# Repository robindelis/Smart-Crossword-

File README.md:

# Smart Crossword Board

A connected wooden crossword board: **older parents or grandparents play with physical wooden tiles on a board at home, while family members play their turns from an app on their phones.**

---

## What It Is

1. **Real Wooden Tiles**: 100 wooden letter tiles with hidden radio tags (NFC) inside.
2. **Simple for Older Players**: No phone needed at the board. A built-in screen and speaker announce opponent moves and show where to place tiles.
3. **Play from Anywhere**: Family members make moves and send short voice notes from their phones.
4. **Automatic Scoring**: The board checks the official dictionary and calculates double/triple scores automatically.

---

## System Overview

```
                                  [ Smart Crossword Board ]
                                             │
      ┌──────────────────────────────────────┼──────────────────────────────────────┐
      ▼                                      ▼                                      ▼
[ Tile Sensors ]                       [ Screen & Audio ]                     [ Power & Turntable ]
• 15x15 (225) antenna grid             • Dual-core microcontroller            • 3.7V 3000mAh battery
• 16-channel switch chips              • 4.3" high-contrast screen            • Magnetic power cable
• 13.56 MHz NFC reader                 • 3W speaker for voice audio           • 360° turntable ring
• 100 tagged wooden tiles              • Offline dictionary in memory         • Wooden enclosure
```

---

## Repository Folders

```
.
├── AGENTS.md               # Team rules and agent list
├── README.md               # This file
├── Project_Cockpit.canvas  # Visual board for Obsidian
├── docs/                   # Project documentation, specs, sourcing & state
│   ├── PROJECT_STATE.md    # Current phase, decisions, and roadmap
│   ├── Project_Tasks.md    # Task list (Kanban format)
│   └── ...                 # RFID specs, software architecture, candidate lists
├── .agents/
│   └── agents/             # Agent guidelines (hardware, code, sales, testing)
├── commercial/             # Market research, video script, ad templates
├── hardware/               # Circuit schematics and board layouts
├── firmware/               # Microcontroller code
├── software/               # Native Android companion app
└── tests/                  # Test scripts and benchmarks
```

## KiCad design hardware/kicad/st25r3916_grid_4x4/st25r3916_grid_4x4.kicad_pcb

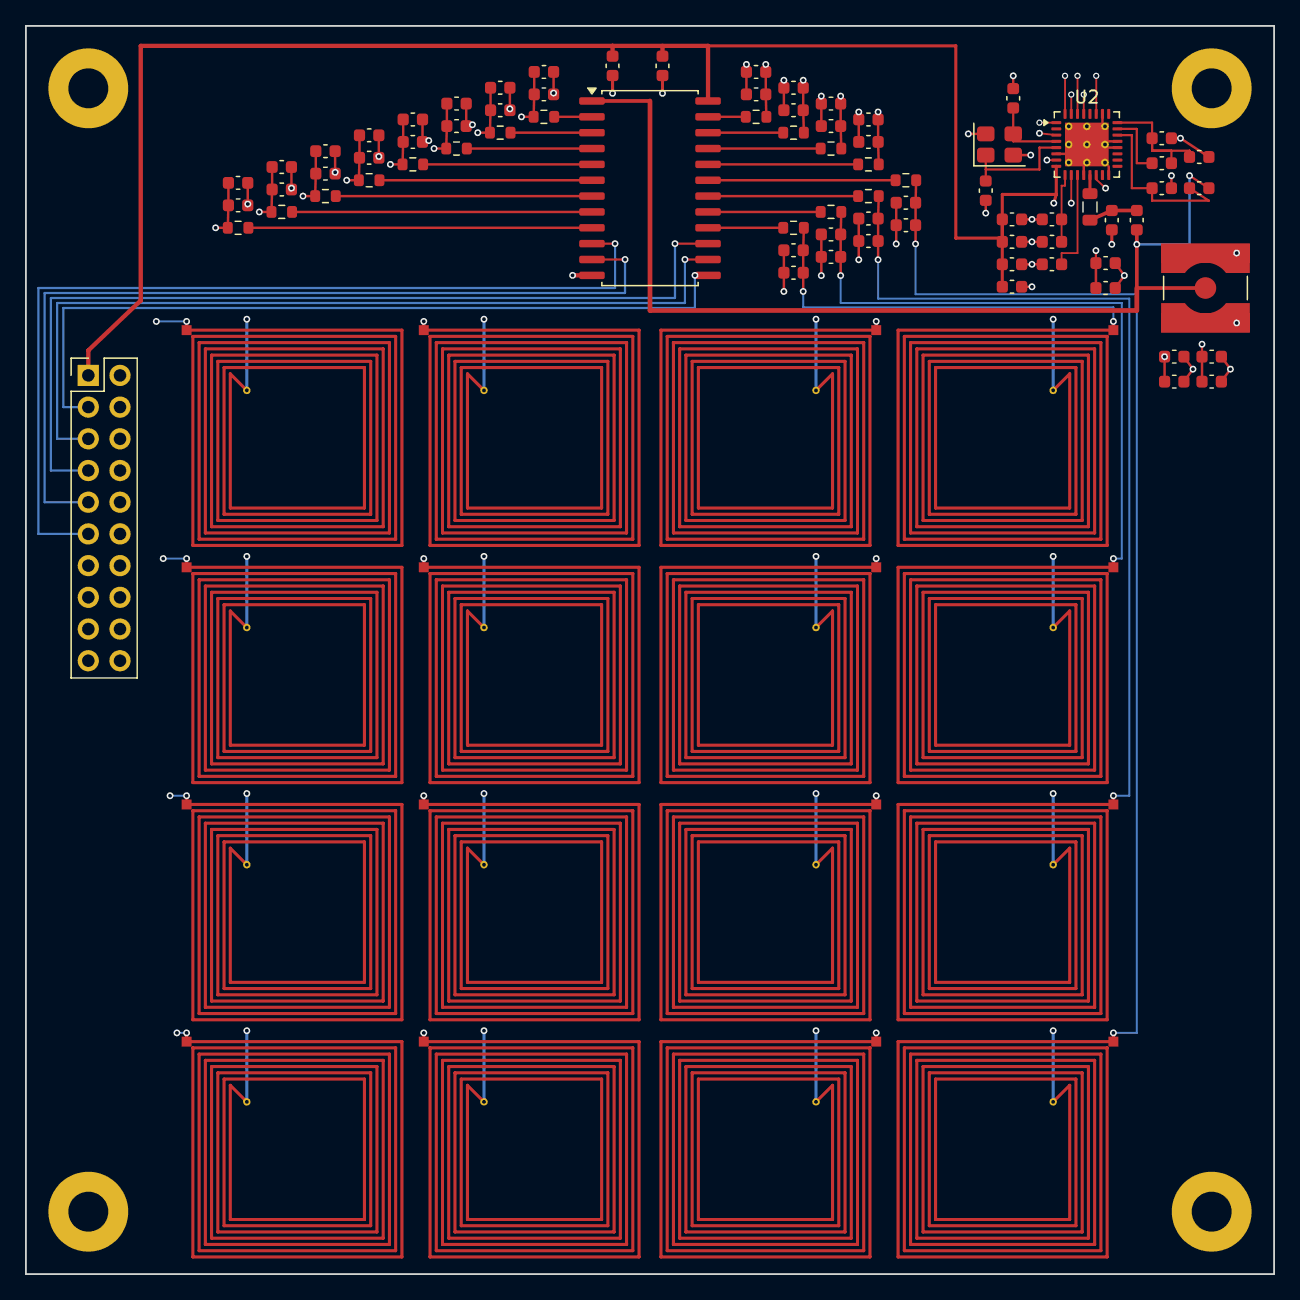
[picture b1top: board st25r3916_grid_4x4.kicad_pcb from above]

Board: 4 copper layers, 100.0 x 100.0 mm, 98 parts (0 on the bottom side), 58 nets.

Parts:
C17: 0.1uF; C_0603_1608Metric
C18, C26: 10uF; C_0603_1608Metric
C20, C24, C33, C35: 1uF; C_0603_1608Metric
C21, C25, C29, C31, C36: 10nF; C_0603_1608Metric
C22, C23: 12pF; C_0603_1608Metric
C27, C34: 100nF; C_0603_1608Metric
C28, C30, C32: 2.2uF; C_0603_1608Metric
C37: 180pF; C_0603_1608Metric
C38, C41: 150pF; C_0603_1608Metric
C39: 18pF; C_0603_1608Metric
C40: 10pF; C_0603_1608Metric
Ca1, Ca2, Ca3, Ca4, Ca5, Ca6, Ca7, Ca8, Ca9, Ca10, Ca11, Ca12, Ca13, Ca14, Ca15, Ca16: 100pF; C_0603_1608Metric
Cb1, Cb2, Cb3, Cb4, Cb5, Cb6, Cb7, Cb8, Cb9, Cb10, Cb11, Cb12, Cb13, Cb14, Cb15, Cb16: 22pF; C_0603_1608Metric
H1, H2, H3, H4: MountingHole_M3; MountingHole_3.2mm_M3_Pad
J1: Host_Header_2x10; PinHeader_2x10_P2.54mm_Vertical
J3: RF_TEST_SMA; SMA_Amphenol_132134-10_Vertical
L1, L2, L3, L4, L5, L6, L7, L8, L9, L10, L11, L12, L13, L14, L15, L16: 1.26uH
L17: 470nH; L_0805_2012Metric
R1, R2, R3, R4, R5, R6, R7, R8, R9, R10, R11, R12, R13, R14, R15, R16: 1.5R; R_0603_1608Metric
U1: CD74HC4067M; SOIC-24W_7.5x15.4mm_P1.27mm
U2: ST25R3916B-AQFT; VQFN-32-1EP_5x5mm_P0.5mm_EP3.5x3.5mm_ThermalVias
Y1: 27.12MHz; Crystal_SMD_3225-4Pin_3.2x2.5mm

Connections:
/+3.3V: J1.12, U2.1
/+5V: C17.1, C18.1, C26.1, C27.1, C30.1, C31.1, J1.1, U1.24, U2.8, U2.10
/AGDC: C35.1, C36.1, C38.2, U2.24
/GND: C17.2, C18.2, C20.2, C21.2, C22.2, C23.2, C24.2, C25.2, C26.2, C27.2, C28.2, C29.2, C30.2, C31.2, C32.2, C33.2, C34.2, C35.2, C36.2, C37.2, C41.2, Ca1.2, Ca2.2, Ca3.2, Ca4.2, Ca5.2, Ca6.2, Ca7.2, Ca8.2, Ca9.2, Ca10.2, Ca11.2, Ca12.2, Ca13.2, Ca14.2, Ca15.2, Ca16.2, Cb1.2, Cb2.2, Cb3.2, Cb4.2, Cb5.2, Cb6.2, Cb7.2, Cb8.2, Cb9.2, Cb10.2, Cb11.2, Cb12.2, Cb13.2, Cb14.2, Cb15.2, Cb16.2, H1.1, H2.1, H3.1, H4.1, J1.17, J1.18, J1.19, J1.20, J3.2, L1.2, L2.2, L3.2, L4.2, L5.2, L6.2, L7.2, L8.2, L9.2, L10.2, L11.2, L12.2, L13.2, L14.2, L15.2, L16.2, U1.12, U2.6, U2.12, U2.16, U2.20, U2.21, U2.26, U2.33, Y1.2, Y1.4
/MUX_EN: J1.7, U1.15
/MUX_S0: J1.11, U1.10
/MUX_S1: J1.9, U1.11
/MUX_S2: J1.5, U1.14
/MUX_S3: J1.3, U1.13
/OSC_IN: C23.1, U2.5, Y1.1
/OSC_OUT: C22.1, U2.4, Y1.3
/RFI1: C40.2, C41.1, U2.22
/RFI2: C38.1, U2.23
/RFO1: L17.1, U2.13
/RF_CH0: R13.2, U1.9
/RF_CH1: R9.2, U1.8
/RF_CH2: R5.2, U1.7
/RF_CH3: R1.2, U1.6
/RF_CH4: R14.2, U1.5
/RF_CH5: R10.2, U1.4
/RF_CH6: R6.2, U1.3
/RF_CH7: R2.2, U1.2
/RF_CH8: R15.2, U1.23
/RF_CH9: R11.2, U1.22
/RF_CH10: R7.2, U1.21
/RF_CH11: R3.2, U1.20
/RF_CH12: R16.2, U1.19
/RF_CH13: R12.2, U1.18
/RF_CH14: R8.2, U1.17
/RF_CH15: R4.2, U1.16
/RF_COIL_1: Ca1.1, Cb1.1, L1.1, R1.1
/RF_COIL_2: Ca2.1, Cb2.1, L2.1, R2.1
/RF_COIL_3: Ca3.1, Cb3.1, L3.1, R3.1
/RF_COIL_4: Ca4.1, Cb4.1, L4.1, R4.1
/RF_COIL_5: Ca5.1, Cb5.1, L5.1, R5.1
/RF_COIL_6: Ca6.1, Cb6.1, L6.1, R6.1
/RF_COIL_7: Ca7.1, Cb7.1, L7.1, R7.1
/RF_COIL_8: Ca8.1, Cb8.1, L8.1, R8.1
/RF_COIL_9: Ca9.1, Cb9.1, L9.1, R9.1
/RF_COIL_10: Ca10.1, Cb10.1, L10.1, R10.1
/RF_COIL_11: Ca11.1, Cb11.1, L11.1, R11.1
/RF_COIL_12: Ca12.1, Cb12.1, L12.1, R12.1
/RF_COIL_13: Ca13.1, Cb13.1, L13.1, R13.1
/RF_COIL_14: Ca14.1, Cb14.1, L14.1, R14.1
/RF_COIL_15: Ca15.1, Cb15.1, L15.1, R15.1
/RF_COIL_16: Ca16.1, Cb16.1, L16.1, R16.1
/RF_FLT: C37.1, C39.1, L17.2
/RF_SIG: C39.2, C40.1, J3.1, U1.1
/SPI_CS: J1.4, U2.29
/SPI_MISO: J1.10, U2.32
/SPI_MOSI: J1.8, U2.31
/SPI_SCK: J1.6, U2.30
/ST_IRQ: J1.2, U2.27
/VDD_A: C24.1, C25.1, U2.7
/VDD_AM: C32.1, U2.11
/VDD_D: C20.1, C21.1, U2.3
/VDD_DR: C33.1, C34.1, U2.14
/VDD_RF: C28.1, C29.1, U2.9

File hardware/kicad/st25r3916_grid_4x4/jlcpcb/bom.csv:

Comment,Designator,Footprint,LCSC Part #,Quantity
0.1uF,C17,C_0603_1608Metric,C14664,1
1.5R,"R1,R10,R11,R12,R13,R14,R15,R16,R2,R3,R4,R5,R6,R7,R8,R9",R_0603_1608Metric,C22790,16
100nF,"C27,C34",C_0603_1608Metric,C14664,2
100pF,"Ca1,Ca2,Ca3,Ca4,Ca5,Ca6,Ca7,Ca8,Ca9,Ca10,Ca11,Ca12,Ca13,Ca14,Ca15,Ca16",C_0603_1608Metric,C14663,16
10nF,"C21,C25,C29,C31,C36",C_0603_1608Metric,C57112,5
10pF,C40,C_0603_1608Metric,C1642,1
10uF,"C18,C26",C_0603_1608Metric,C19702,2
12pF,"C22,C23",C_0603_1608Metric,C1648,2
150pF,"C38,C41",C_0603_1608Metric,C1598,2
180pF,C37,C_0603_1608Metric,C1600,1
18pF,C39,C_0603_1608Metric,C1651,1
1uF,"C20,C24,C33,C35",C_0603_1608Metric,C15849,4
2.2uF,"C28,C30,C32",C_0603_1608Metric,C23630,3
22pF,"Cb1,Cb2,Cb3,Cb4,Cb5,Cb6,Cb7,Cb8,Cb9,Cb10,Cb11,Cb12,Cb13,Cb14,Cb15,Cb16",C_0603_1608Metric,C1653,16
27.12MHz,Y1,Crystal_SMD_3225-4Pin_3.2x2.5mm,C383929,1
470nH,L17,L_0805_2012Metric,C1045,1
CD74HC4067M,U1,SOIC-24W_7.5x15.4mm_P1.27mm,C109598,1
Host_Header_2x10,J1,PinHeader_2x10_P2.54mm_Vertical,,1
RF_TEST_SMA,J3,SMA_Amphenol_132134-10_Vertical,,1
ST25R3916B-AQFT,U2,VQFN-32-1EP_5x5mm_P0.5mm_EP3.5x3.5mm_ThermalVias,C2943312,1

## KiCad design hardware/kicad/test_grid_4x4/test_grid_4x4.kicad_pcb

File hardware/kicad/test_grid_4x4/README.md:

# Phase 1: 4x4 NFC Test Board

## 1. Purpose
This 4x4 circuit board is the Phase 1 test vehicle for the Smart Crossword Board project. It tests reading 16 RFID letter tiles through 2.0mm to 2.5mm hardwood before building the full 15x15 (225-cell) commercial board.

It verifies three physical requirements:
1. **Hardwood Penetration**: Reliable tag reads through 2.0mm–2.5mm oak or walnut veneer.
2. **Scan Speed**: Reading all 16 cells in under 40 milliseconds using an analog multiplexer.
3. **Cross-talk Isolation**: Zero false reads on neighboring empty cells when adjacent cells have tiles.

---

## 2. Key Specifications

| Parameter | Value | Notes |
| :--- | :--- | :--- |
| **Grid Dimensions** | 4 x 4 (16 cells) | Pitch: 19.0 mm (matches Scrabble tiles) |
| **Active Scan Area** | 76.0 mm x 76.0 mm | Centered on board |
| **PCB Dimensions** | 100.0 mm x 100.0 mm | Standard 10cm x 10cm low-cost pool |
| **Layers** | 4 layers | F.Cu (RF), In1.Cu (GND), In2.Cu (Pwr/Sig), B.Cu (Return/GND) |
| **Coil Outer Size** | 17.5 mm x 17.5 mm | Fits comfortably within 19mm square |
| **Coil Geometry** | 7 turns, 0.25mm trace, 0.25mm space | Planar square spiral on F.Cu |
| **Coil Inductance ($L$)** | **1.262 µH** | Wheeler model verified |
| **Tuning Capacitor ($C$)** | **100 pF** (50V C0G / NP0 0603) | Resonant frequency: 13.56 MHz |
| **Damping Resistor ($R$)** | **3.3 Ω** (1% 0603) | Target loaded Q-factor: 25 |
| **RF Multiplexer** | CD74HC4067SM96 (SOIC-24) | 16-channel analog switch (LCSC C7406) |
| **Mounting** | 4x M3 screw holes (3.2mm drill) | 5.0mm inset from corners |

---

## 3. Connector Pinouts

### J1: Host Controller Header (2x10, 2.54mm Pitch)
Connects directly to an ESP32-S3 DevKit or breadboard:

| Pin | Net | Function | Pin | Net | Function |
| :--- | :--- | :--- | :--- | :--- | :--- |
| **1** | +3.3V | Power In | **2** | +3.3V | Power In |
| **3** | MUX_S3 | Address bit 3 | **4** | GPIO_AUX | Spare tactile button / LED |
| **5** | MUX_S2 | Address bit 2 | **6** | I2C_SDA | Spare I2C data |
| **7** | MUX_EN | MUX active-low enable | **8** | I2C_SCL | Spare I2C clock |
| **9** | MUX_S1 | Address bit 1 | **10** | NFC_IRQ | NFC interrupt |
| **11** | MUX_S0 | Address bit 0 | **12** | NFC_RST | NFC reset |
| **13** | GND | Ground | **14** | SPI_MOSI | NFC SPI data out |
| **15** | GND | Ground | **16** | SPI_CS | NFC SPI chip select |
| **17** | GND | Ground | **18** | SPI_SCK | NFC SPI clock |
| **19** | GND | Ground | **20** | SPI_MISO | NFC SPI data in |

### J2: NFC Transceiver Header (1x10, 2.54mm Pitch)
Connects to an ST25R3916 or PN532 transceiver breakout:
1. `RF_SIG` (Multiplexer common RF output/input)
2. `GND`
3. `+3.3V`
4. `GND`
5. `SPI_SCK`
6. `SPI_MISO`
7. `SPI_MOSI`
8. `SPI_CS`
9. `NFC_IRQ`
10. `NFC_RST`

### J3: SMA RF Test Port
Standard 50Ω SMA coaxial connector wired to `RF_SIG` for connecting an oscilloscope or Vector Network Analyzer (VNA) during bench characterization.

---

## 4. Verification & DRC Status (KiCad 10.0.6)

* **Design Rule Check (DRC)**: **0 errors, 0 warnings, 0 violations**.
* **Unconnected Items**: **0 unconnected nets** (all 49 nets fully routed).
* **Layer Stackup**:
  * **F.Cu**: 16 planar spiral coils (1.26 µH, 7 turns), RF_SIG 50Ω trace, 0603 matching network components.
  * **In1.Cu**: Continuous solid GND plane with 16 dedicated keepout apertures ($18.5\text{mm} \times 18.5\text{mm}$) preventing RF eddy current damping.
  * **In2.Cu**: 100% planar coil feed routing for Columns A, B, C, and D, plus SPI bus lines.
  * **B.Cu**: Bottom GND plane with thermal relief spokes to coil centers, concentric MUX control lines, and +3.3V power bus.

---

## 5. Bill of Materials (BOM)

| Designator | Description | Footprint | LCSC Part # | Unit Price (100 qty) |
| :--- | :--- | :--- | :--- | :--- |
| **U1** | CD74HC4067SM96 16-Ch MUX | SOIC-24 | C496123 | $0.28 |
| **C1–C16** | 100pF 50V C0G 5% | 0603 | C14665 | $0.005 |
| **R1–R16** | 3.3Ω 1% 1/10W | 0603 | C22979 | $0.003 |
| **C17** | 0.1µF 50V X7R 10% (Decoupling) | 0603 | C14663 | $0.003 |
| **C18** | 10µF 10V X5R 10% (Decoupling) | 0805 | C15850 | $0.015 |
| **J1** | 2x10 2.54mm Male Pin Header | THT 2x10 | C22588 | $0.15 |
| **J2** | 1x10 2.54mm Male Pin Header | THT 1x10 | C22585 | $0.08 |
| **J3** | SMA End Launch / Edge Female | SMA-TH | C2837267 | $0.65 |
| **H1–H4** | M3 Mounting Holes | 3.2mm PTH | N/A | $0.00 |

**Total BOM cost for 4x4 test board**: ~$1.45 (excluding PCB fab).

---

## 6. How to Open and Review in KiCad

1. Open your Linux application launcher.
2. Select **KiCad (EDA Suite)** (the top entry with the blue icon).
3. In KiCad, go to **File -> Open Project...**.
4. Browse to `hardware/kicad/test_grid_4x4/test_grid_4x4.kicad_pro`.
5. Double-click `test_grid_4x4.kicad_sch` to view the schematic, or `test_grid_4x4.kicad_pcb` to view the board layout.
6. In the PCB editor, press **Alt + 3** (or menu **View -> 3D Viewer**) to interact with the 3D model.

---

## 7. Prototype (4x4) Shopping List Compatibility & Wiring Guide

This section verifies compatibility with the components procured in [[Prototype_4x4_Shopping_List|Prototype 4x4 Shopping List]]:

### Component Compatibility Matrix

| Shopping List Item | Selected Model | PCB Compatibility | Connection / Assembly Notes |
| :--- | :--- | :--- | :--- |
| **Letter Tiles (16 needed)** | 200 Pcs Wooden Scrabble Tiles (`B0GH7LXL2K`) | ✅ **100% Compatible** | 19.0 x 19.0 x 4.8 mm wood tiles align 1:1 with the 19.0mm PCB coil pitch. |
| **13.56 MHz NFC Tags** | 60 Pcs NTAG213 Stickers 25mm (`B0HC2ZKQLQ`) | ✅ **100% Compatible (RF)** | 13.56 MHz ISO 14443A matches resonant LC tank. For bench testing, 25mm stickers can be affixed centered on tiles or test veneer. |
| **Host Microcontroller** | ESP32-S3 DevKitC-1 N16R8 (`B0GXF14RRM`) | ✅ **100% Compatible** | 3.3V logic matches +3.3V rail. Connects to J1 via 20-pin IDC ribbon or Dupont jumper wires. |
| **16-Ch Multiplexer** | DollaTek CD74HC4067 Breakout (`B07PPKRVGW`) | ⚠️ **Footprint Variant Note** | PCB footprint U1 is **SOIC-24 SMD** (`CD74HC4067SM96`, LCSC C7406) for JLCPCB PCBA. The Amazon DollaTek breakout module (24-pin DIP) is for breadboard testing. Order JLCPCB PCBA or bare SOIC-24 IC for this PCB. |
| **NFC Reader Module** | PN532 V3 RFID/NFC Breakout Kit (`B0C9DTJMLQ`) | ⚠️ **RF Tap Required** | Connect SPI signals (SCK, MISO, MOSI, SS/CS, IRQ, RST, 3.3V, GND) to J2 via Dupont leads. To drive PCB coils, link the PN532 RF stage to J3 (SMA) or J2 Pin 1 (`RF_SIG`) via a 50Ω coaxial pigtail. |
| **Rotating Turntable** | QWORK Square Bearing 71x71mm (`B0B3X7R961`) | ✅ **100% Compatible** | Mounts centered underneath the 3D-printed base enclosure tray; zero interference with PCB. |
| **Color Display Screen** | 3.5" TFT SPI 480x320 (`B0BZXX1QFM`) | ✅ **100% Compatible** | Off-board peripheral wired directly to ESP32-S3 host GPIOs. |
| **Audio DAC Amp & Speaker** | MAX98357A I2S Amp (`B0F21T7Q3P`) + 40mm 4Ω Speaker | ✅ **100% Compatible** | Off-board I2S peripheral wired directly to ESP32-S3 host GPIOs. |
| **Hardware Fasteners** | 440 Pcs M3 Button Head Screws & Nuts (`B0B3MGZ7T2`) | ✅ **100% Compatible** | M3x8 / M3x10 screws seat perfectly in the 4x 3.2mm corner mounting holes (H1–H4). |
| **Anti-Skid Bumper Feet** | Silicone Bumper Feet 10mm (`B08GKP4311`) | ✅ **100% Compatible** | Fits bottom locating recesses in 3D-printed base enclosure. |

### J1 (ESP32-S3 Host) Wiring Map

| Header J1 Pin | Net | ESP32-S3 DevKit Pin | Function |
| :--- | :--- | :--- | :--- |
| **Pin 1, 2** | `+3.3V` | `3V3` | Power Supply |
| **Pin 3** | `MUX_S3` | `GPIO 4` | Multiplexer Address Bit 3 |
| **Pin 5** | `MUX_S2` | `GPIO 5` | Multiplexer Address Bit 2 |
| **Pin 7** | `MUX_EN` | `GPIO 6` | Multiplexer Enable (Active Low) |
| **Pin 9** | `MUX_S1` | `GPIO 7` | Multiplexer Address Bit 1 |
| **Pin 11** | `MUX_S0` | `GPIO 15` | Multiplexer Address Bit 0 |
| **Pin 13, 15, 17, 19** | `GND` | `GND` | Ground Reference |
| **Pin 4** | `GPIO_AUX` | `GPIO 16` | Spare / Tactile Button / LED |
| **Pin 6** | `I2C_SDA` | `GPIO 8` | Spare I2C Data |
| **Pin 8** | `I2C_SCL` | `GPIO 9` | Spare I2C Clock |
| **Pin 10** | `NFC_IRQ` | `GPIO 10` | NFC Reader Interrupt |
| **Pin 12** | `NFC_RST` | `GPIO 11` | NFC Reader Reset |
| **Pin 14** | `SPI_MOSI`| `GPIO 13` | SPI Data Host -> NFC |
| **Pin 16** | `SPI_CS` | `GPIO 14` | SPI Chip Select |
| **Pin 18** | `SPI_SCK` | `GPIO 12` | SPI Clock |
| **Pin 20** | `SPI_MISO`| `GPIO 21` | SPI Data NFC -> Host |

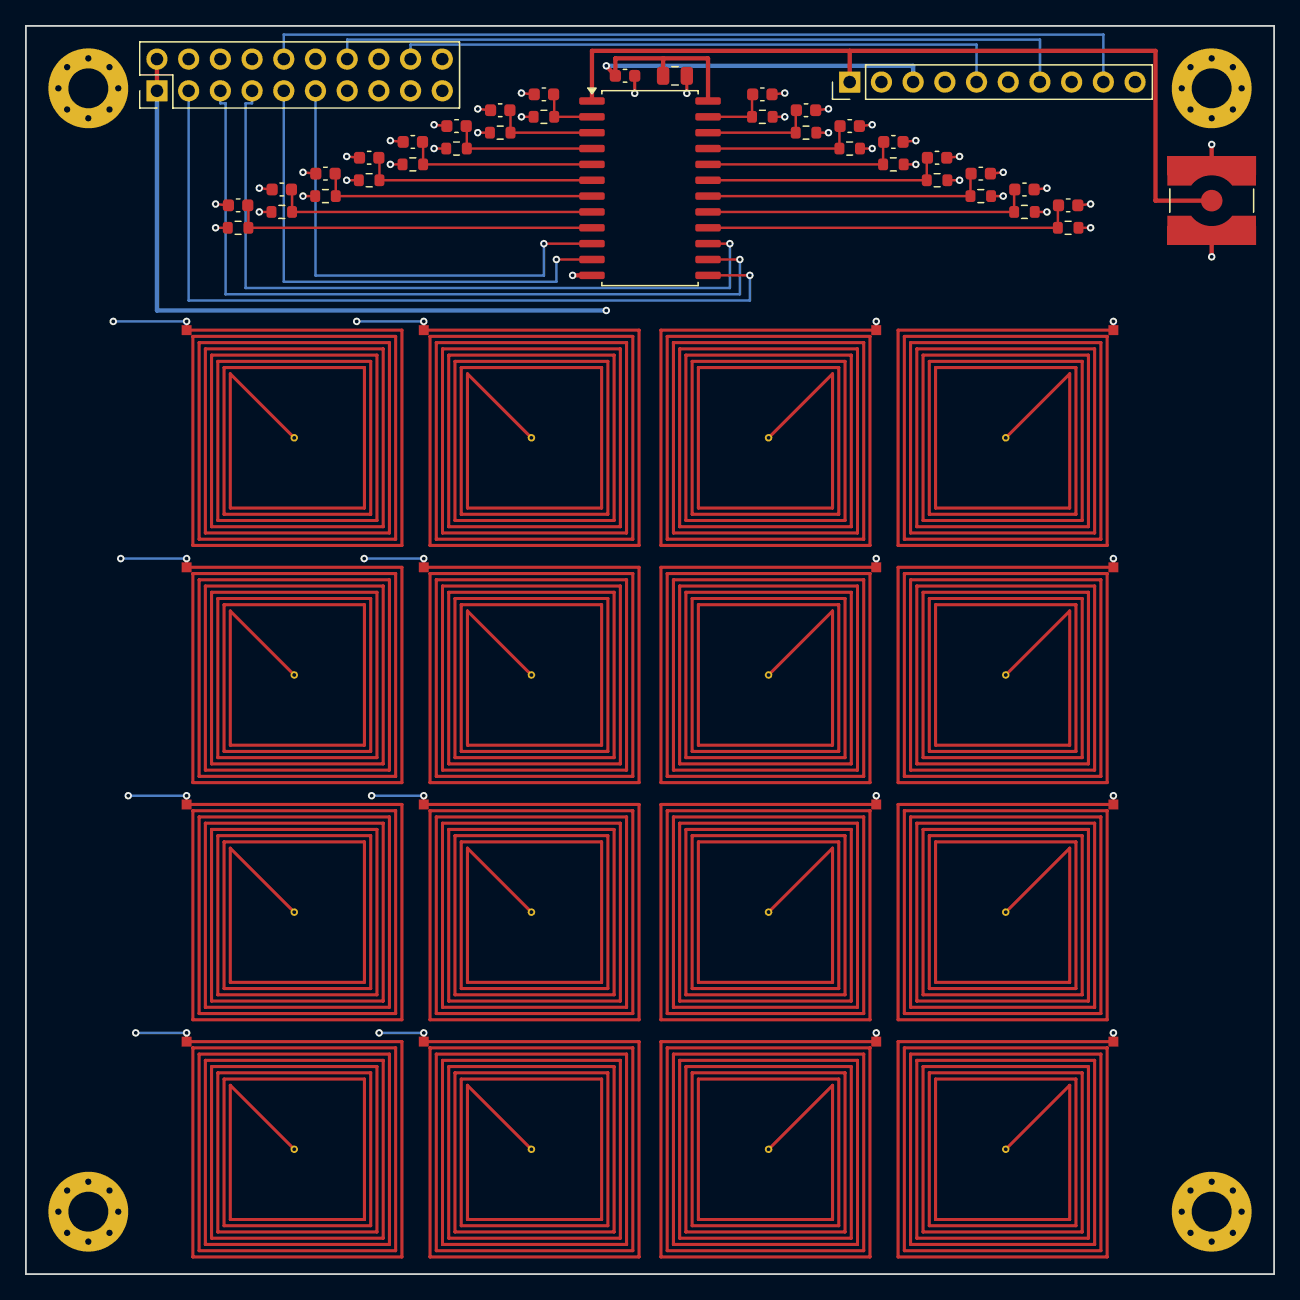
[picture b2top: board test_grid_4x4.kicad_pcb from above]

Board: 4 copper layers, 100.0 x 100.0 mm, 58 parts (0 on the bottom side), 46 nets.

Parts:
C1, C2, C3, C4, C5, C6, C7, C8, C9, C10, C11, C12, C13, C14, C15, C16: 100pF; C_0603_1608Metric
C17: 0.1uF; C_0603_1608Metric
C18: 10uF; C_0805_2012Metric
H1, H2, H3, H4: MountingHole_M3; MountingHole_3.2mm_M3_Pad_Via
J1: HOST_BUS; PinHeader_2x10_P2.54mm_Vertical
J2: NFC_MODULE; PinHeader_1x10_P2.54mm_Vertical
J3: RF_TEST; SMA_Amphenol_132134-10_Vertical
L1, L2, L3, L4, L5, L6, L7, L8, L9, L10, L11, L12, L13, L14, L15, L16: 1.26uH
R1, R2, R3, R4, R5, R6, R7, R8, R9, R10, R11, R12, R13, R14, R15, R16: 3.3; R_0603_1608Metric
U1: CD74HC4067M; SOIC-24W_7.5x15.4mm_P1.27mm

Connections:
+3.3V: C17.1, C18.1, J1.1, J1.2, J2.3, U1.24
GND: C1.2, C2.2, C3.2, C4.2, C5.2, C6.2, C7.2, C8.2, C9.2, C10.2, C11.2, C12.2, C13.2, C14.2, C15.2, C16.2, C17.2, C18.2, H1.1, H2.1, H3.1, H4.1, J1.13, J1.15, J1.17, J1.19, J2.2, J2.4, J3.2, L1.2, L2.2, L3.2, L4.2, L5.2, L6.2, L7.2, L8.2, L9.2, L10.2, L11.2, L12.2, L13.2, L14.2, L15.2, L16.2, U1.12
MUX_EN: J1.7, U1.15
MUX_S0: J1.11, U1.10
MUX_S1: J1.9, U1.11
MUX_S2: J1.5, U1.14
MUX_S3: J1.3, U1.13
NFC_IRQ: J1.10, J2.9
NFC_RST: J1.12, J2.10
RF_CH0: C13.1, R13.1, U1.9
RF_CH1: C9.1, R9.1, U1.8
RF_CH2: C5.1, R5.1, U1.7
RF_CH3: C1.1, R1.1, U1.6
RF_CH4: C14.1, R14.1, U1.5
RF_CH5: C10.1, R10.1, U1.4
RF_CH6: C6.1, R6.1, U1.3
RF_CH7: C2.1, R2.1, U1.2
RF_CH8: C15.1, R15.1, U1.23
RF_CH9: C11.1, R11.1, U1.22
RF_CH10: C7.1, R7.1, U1.21
RF_CH11: C3.1, R3.1, U1.20
RF_CH12: C16.1, R16.1, U1.19
RF_CH13: C12.1, R12.1, U1.18
RF_CH14: C8.1, R8.1, U1.17
RF_CH15: C4.1, R4.1, U1.16
RF_COIL_1: L1.1, R1.2
RF_COIL_2: L2.1, R2.2
RF_COIL_3: L3.1, R3.2
RF_COIL_4: L4.1, R4.2
RF_COIL_5: L5.1, R5.2
RF_COIL_6: L6.1, R6.2
RF_COIL_7: L7.1, R7.2
RF_COIL_8: L8.1, R8.2
RF_COIL_9: L9.1, R9.2
RF_COIL_10: L10.1, R10.2
RF_COIL_11: L11.1, R11.2
RF_COIL_12: L12.1, R12.2
RF_COIL_13: L13.1, R13.2
RF_COIL_14: L14.1, R14.2
RF_COIL_15: L15.1, R15.2
RF_COIL_16: L16.1, R16.2
RF_SIG: J2.1, J3.1, U1.1
SPI_CS: J1.16, J2.8
SPI_MISO: J1.20, J2.6
SPI_MOSI: J1.14, J2.7
SPI_SCK: J1.18, J2.5

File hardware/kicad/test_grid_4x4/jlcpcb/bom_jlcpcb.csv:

Comment,Designator,Footprint,LCSC Part #
100pF 50V C0G 5%,"C1, C2, C3, C4, C5, C6, C7, C8, C9, C10, C11, C12, C13, C14, C15, C16",C_0603_1608Metric,C14405
3.3Ω 1% 1/10W,"R1, R2, R3, R4, R5, R6, R7, R8, R9, R10, R11, R12, R13, R14, R15, R16",R_0603_1608Metric,C22971
0.1uF 50V X7R 10%,C17,C_0603_1608Metric,C14663
10uF 10V X5R 10%,C18,C_0805_2012Metric,C15850
CD74HC4067SM96 16-Ch MUX,U1,SOIC-24W_7.5x15.4mm_P1.27mm,C7406

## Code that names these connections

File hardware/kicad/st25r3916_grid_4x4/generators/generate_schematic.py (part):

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\t\t\t(pin power_in line (at -20.32 -12.70 0) (length 2.54) (name "VDD_TX" (effects (font (size 1.27 1.27)))) (number "10" (effects (font (size 1.27 1.27)))))
\t\t\t(pin power_out line (at 20.32 7.62 180) (length 2.54) (name "VDD_AM" (effects (font (size 1.27 1.27)))) (number "11" (effects (font (size 1.27 1.27)))))
\t\t\t(pin power_in line (at -5.08 25.4 270) (length 2.54) (name "GND_DR1" (effects (font (size 1.27 1.27)))) (number "12" (effects (font (size 1.27 1.27)))))
\t\t\t(pin output line (at 20.32 -17.78 180) (length 2.54) (name "RFO1" (effects (font (size 1.27 1.27)))) (number "13" (effects (font (size 1.27 1.27)))))
\t\t\t(pin power_out line (at 20.32 2.54 180) (length 2.54) (name "VDD_DR" (effects (font (size 1.27 1.27)))) (number "14" (effects (font (size 1.27 1.27)))))
\t\t\t(pin output line (at 20.32 -15.24 180) (length 2.54) (name "RFO2" (effects (font (size 1.27 1.27)))) (number "15" (effects (font (size 1.27 1.27)))))
\t\t\t(pin power_in line (at 0.00 25.4 270) (length 2.54) (name "GND_DR2" (effects (font (size 1.27 1.27)))) (number "16" (effects (font (size 1.27 1.27)))))
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\t\t\t(pin passive line (at -2.54 -25.4 90) (length 2.54) (name "AAT_B" (effects (font (size 1.27 1.27)))) (number "19" (effects (font (size 1.27 1.27)))))
\t\t\t(pin input line (at -20.32 12.70 0) (length 2.54) (name "I2C_EN" (effects (font (size 1.27 1.27)))) (number "20" (effects (font (size 1.27 1.27)))))
\t\t\t(pin power_in line (at 5.08 25.4 270) (length 2.54) (name "VSS" (effects (font (size 1.27 1.27)))) (number "21" (effects (font (size 1.27 1.27)))))
\t\t\t(pin input line (at 20.32 -10.16 180) (length 2.54) (name "RFI1" (effects (font (size 1.27 1.27)))) (number "22" (effects (font (size 1.27 1.27)))))
\t\t\t(pin input line (at 20.32 -7.62 180) (length 2.54) (name "RFI2" (effects (font (size 1.27 1.27)))) (number "23" (effects (font (size 1.27 1.27)))))
\t\t\t(pin power_out line (at 20.32 -2.54 180) (length 2.54) (name "AGDC" (effects (font (size 1.27 1.27)))) (number "24" (effects (font (size 1.27 1.27)))))
\t\t\t(pin passive line (at 2.54 -25.4 90) (length 2.54) (name "TAD1" (effects (font (size 1.27 1.27)))) (number "25" (effects (font (size 1.27 1.27)))))
\t\t\t(pin power_in line (at 10.16 25.4 270) (length 2.54) (name "GND_A" (effects (font (size 1.27 1.27)))) (number "26" (effects (font (size 1.27 1.27)))))
\t\t\t(pin output line (at -20.32 7.62 0) (length 2.54) (name "IRQ" (effects (font (size 1.27 1.27)))) (number "27" (effects (font (size 1.27 1.27)))))
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    connect_pin(u2_x, u2_y, pins_st25, 1, "+3.3V", -5.08, 0, 180)
    connect_pin(u2_x, u2_y, pins_st25, 8, "+5V", -5.08, 0, 180)
    connect_pin(u2_x, u2_y, pins_st25, 10, "+5V", -5.08, 0, 180)
    connect_pin(u2_x, u2_y, pins_st25, 29, "SPI_CS", -5.08, 0, 180)
    connect_pin(u2_x, u2_y, pins_st25, 30, "SPI_SCK", -5.08, 0, 180)
    connect_pin(u2_x, u2_y, pins_st25, 31, "SPI_MOSI", -5.08, 0, 180)
    connect_pin(u2_x, u2_y, pins_st25, 32, "SPI_MISO", -5.08, 0, 180)
    connect_pin(u2_x, u2_y, pins_st25, 27, "ST_IRQ", -5.08, 0, 180)
    connect_pin(u2_x, u2_y, pins_st25, 20, "GND", -5.08, 0, 180) # I2C_EN = GND for SPI mode

    nc_pin(u2_x, u2_y, pins_st25, 2)  # TAD2
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    nc_pin(u2_x, u2_y, pins_st25, 25) # TAD1

    # RF and Decoupling outputs
    connect_pin(u2_x, u2_y, pins_st25, 13, "RFO1", 5.08, 0, 0)
    connect_pin(u2_x, u2_y, pins_st25, 22, "RFI1", 5.08, 0, 0)
    connect_pin(u2_x, u2_y, pins_st25, 23, "RFI2", 5.08, 0, 0)
    connect_pin(u2_x, u2_y, pins_st25, 24, "AGDC", 5.08, 0, 0)
    connect_pin(u2_x, u2_y, pins_st25, 14, "VDD_DR", 5.08, 0, 0)
    connect_pin(u2_x, u2_y, pins_st25, 9, "VDD_RF", 5.08, 0, 0)
    connect_pin(u2_x, u2_y, pins_st25, 11, "VDD_AM", 5.08, 0, 0)
    connect_pin(u2_x, u2_y, pins_st25, 3, "VDD_D", 5.08, 0, 0)
    connect_pin(u2_x, u2_y, pins_st25, 7, "VDD_A", 5.08, 0, 0)
    connect_pin(u2_x, u2_y, pins_st25, 4, "OSC_OUT", 5.08, 0, 0)
    connect_pin(u2_x, u2_y, pins_st25, 5, "OSC_IN", 5.08, 0, 0)

    # Grounds
    connect_pin(u2_x, u2_y, pins_st25, 6, "GND", 0, 5.08, 270)
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\t\t(pin "4" (uuid "{gen_uuid()}"))
\t\t(instances (project "" (path "/{root_uuid}" (reference "Y1") (unit 1))))
\t)''')
    connect_pin(y1_x, y1_y, pins_xtal, 1, "OSC_OUT", 0, -2.54, 90)
    connect_pin(y1_x, y1_y, pins_xtal, 2, "GND", 2.54, 0, 0)
    connect_pin(y1_x, y1_y, pins_xtal, 3, "OSC_IN", 0, 2.54, 270)
    connect_pin(y1_x, y1_y, pins_xtal, 4, "GND", -2.54, 0, 180)

    # C22 (12pF), C23 (12pF)
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\t)''')
    # Note: L symbol rotated 90 deg -> pin 1 is at (-3.81, 0), pin 2 is at (3.81, 0)
    add_wire(l17_x - 3.81, l17_y, l17_x - 7.62, l17_y)
    add_label("RFO1", l17_x - 7.62, l17_y, 180)
    add_wire(l17_x + 3.81, l17_y, l17_x + 7.62, l17_y)
    add_label("RF_FLT", l17_x + 7.62, l17_y, 0)

    # C37: 180pF EMC filter capacitor to GND
    c37_x, c37_y = 76.2, 147.32
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\t\t(pin "2" (uuid "{gen_uuid()}"))
\t\t(instances (project "" (path "/{root_uuid}" (reference "C37") (unit 1))))
\t)''')
    connect_pin(c37_x, c37_y, pins_c, 1, "RF_FLT", 0, -2.54, 90)
    connect_pin(c37_x, c37_y, pins_c, 2, "GND", 0, 2.54, 270)

    # C39: 18pF Series Matching Capacitor (between RF_FLT and RF_SIG)
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\t\t(instances (project "" (path "/{root_uuid}" (reference "C39") (unit 1))))
\t)''')
    add_wire(c39_x - 3.81, c39_y, c39_x - 7.62, c39_y)
    add_label("RF_FLT", c39_x - 7.62, c39_y, 180)
    add_wire(c39_x + 3.81, c39_y, c39_x + 7.62, c39_y)
    add_label("RF_SIG", c39_x + 7.62, c39_y, 0)

    # Receiver Capacitive Divider: C40 (10pF), C41 (150pF), C38 (150pF)
    # C40 between RF_SIG and RFI1
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\t\t(instances (project "" (path "/{root_uuid}" (reference "C40") (unit 1))))
\t)''')
    add_wire(c40_x - 3.81, c40_y, c40_x - 7.62, c40_y)
    add_label("RF_SIG", c40_x - 7.62, c40_y, 180)
    add_wire(c40_x + 3.81, c40_y, c40_x + 7.62, c40_y)
    add_label("RFI1", c40_x + 7.62, c40_y, 0)

    # C41 (150pF between RFI1 and GND)
    c41_x, c41_y = 76.2, 177.8
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\t\t(pin "2" (uuid "{gen_uuid()}"))
\t\t(instances (project "" (path "/{root_uuid}" (reference "C41") (unit 1))))
\t)''')
    connect_pin(c41_x, c41_y, pins_c, 1, "RFI1", 0, -2.54, 90)
    connect_pin(c41_x, c41_y, pins_c, 2, "GND", 0, 2.54, 270)

    # C38 (150pF between RFI2 and AGDC)
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\t\t(pin "2" (uuid "{gen_uuid()}"))
\t\t(instances (project "" (path "/{root_uuid}" (reference "C38") (unit 1))))
\t)''')
    connect_pin(c38_x, c38_y, pins_c, 1, "RFI2", 0, -2.54, 90)
    connect_pin(c38_x, c38_y, pins_c, 2, "AGDC", 0, 2.54, 270)

    # 6. Multiplexer U1 (CD74HC4067M) at (177.8, 147.32)
    u1_x, u1_y = 177.8, 147.32
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\t\t(instances (project "" (path "/{root_uuid}" (reference "U1") (unit 1))))
\t)''')

    connect_pin(u1_x, u1_y, pins_mux, 1, "RF_SIG", -5.08, 0, 180)
    connect_pin(u1_x, u1_y, pins_mux, 24, "+5V", 0, -5.08, 90)
    connect_pin(u1_x, u1_y, pins_mux, 12, "GND", 0, 5.08, 270)
    connect_pin(u1_x, u1_y, pins_mux, 10, "MUX_S0", -5.08, 0, 180)
    connect_pin(u1_x, u1_y, pins_mux, 11, "MUX_S1", -5.08, 0, 180)
    connect_pin(u1_x, u1_y, pins_mux, 14, "MUX_S2", -5.08, 0, 180)
    connect_pin(u1_x, u1_y, pins_mux, 13, "MUX_S3", -5.08, 0, 180)
    connect_pin(u1_x, u1_y, pins_mux, 15, "MUX_EN", -5.08, 0, 180)

    # Decoupling caps for U1: C17 (0.1uF), C18 (10uF)
    for c_ref, c_val, cx, lcsc in [("C17", "0.1uF", 160.02, "C14663"), ("C18", "10uF", 147.32, "C15850")]:
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\t\t(pin "2" (uuid "{gen_uuid()}"))
\t\t(instances (project "" (path "/{root_uuid}" (reference "J3") (unit 1))))
\t)''')
    connect_pin(sma_x, sma_y, pins_sma, 1, "RF_SIG", -5.08, 0, 180)
    connect_pin(sma_x, sma_y, pins_sma, 2, "GND", 5.08, 0, 0)

    # 9. 4x Mounting Holes H1..H4
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
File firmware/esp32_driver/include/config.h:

#ifndef CONFIG_H
#define CONFIG_H

#include <stdint.h>
#include <stdbool.h>

/* Board Architecture */
#define GRID_ROWS 4
#define GRID_COLS 4
#define GRID_TOTAL_CELLS (GRID_ROWS * GRID_COLS)

/* CD74HC4067 Multiplexer GPIO Pin Assignment (ESP32-S3 DevKitC-1) */
#define PIN_MUX_S0   15  /* J1 Pin 11: Address bit 0 */
#define PIN_MUX_S1   7   /* J1 Pin 9:  Address bit 1 */
#define PIN_MUX_S2   5   /* J1 Pin 5:  Address bit 2 */
#define PIN_MUX_S3   4   /* J1 Pin 3:  Address bit 3 */
#define PIN_MUX_EN   6   /* J1 Pin 7:  Active-Low Enable */

/* PN532 NFC Transceiver SPI Pin Assignment */
#define PIN_SPI_SCK  12  /* J1 Pin 18: SPI Clock */
#define PIN_SPI_MOSI 13  /* J1 Pin 14: Master Out Slave In */
#define PIN_SPI_MISO 21  /* J1 Pin 20: Master In Slave Out */
#define PIN_SPI_CS   14  /* J1 Pin 16: SPI Chip Select */
#define PIN_NFC_IRQ  10  /* J1 Pin 10: NFC Interrupt */
#define PIN_NFC_RST  11  /* J1 Pin 12: NFC Reset */

/* Spare GPIOs */
#define PIN_GPIO_AUX 16  /* J1 Pin 4:  Tactile Button / Debug LED */
#define PIN_I2C_SDA  8   /* J1 Pin 6:  Spare I2C SDA */
#define PIN_I2C_SCL  9   /* J1 Pin 8:  Spare I2C SCL */

/* Timing Constraints (Invariants from wise.md) */
#define MUX_SETTLE_US          20    /* Analog switch propagation + settling delay */
#define NFC_POLL_TIMEOUT_MS    4     /* Max wait time per channel when checking tag presence */
#define SCAN_DEBOUNCE_CYCLES   2     /* Number of consecutive identical reads before state change */
#define SCAN_INTERVAL_IDLE_MS  100   /* Delay between continuous sweep passes */

/* Maximum NFC UID length (4 bytes for MIFARE Classic / Ultralight, 7 bytes for NTAG213) */
#define MAX_UID_LEN            7

#endif /* CONFIG_H */
